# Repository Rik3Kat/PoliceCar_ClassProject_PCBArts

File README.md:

# PoliceCar_ClassProject_PCBArts

Here are the files for my PCB project.
The PCB consists of a simple curcuit: 

one 9V battery that powers everything

eight resistors
                                     
two capacitors
                                      
two transistors
                                      
two LED in the colour red and blue which alternately blink
                                       
four white LED which light up constantly

one slider switch which turns the lights of the curcuit on and off

The board of the PCB is designed in the shape of an old school police car. The curcuit and the footprint parts are fixed to the frontside of the board. 
The actual design of the PCB with the different layers is on the backside of the board.

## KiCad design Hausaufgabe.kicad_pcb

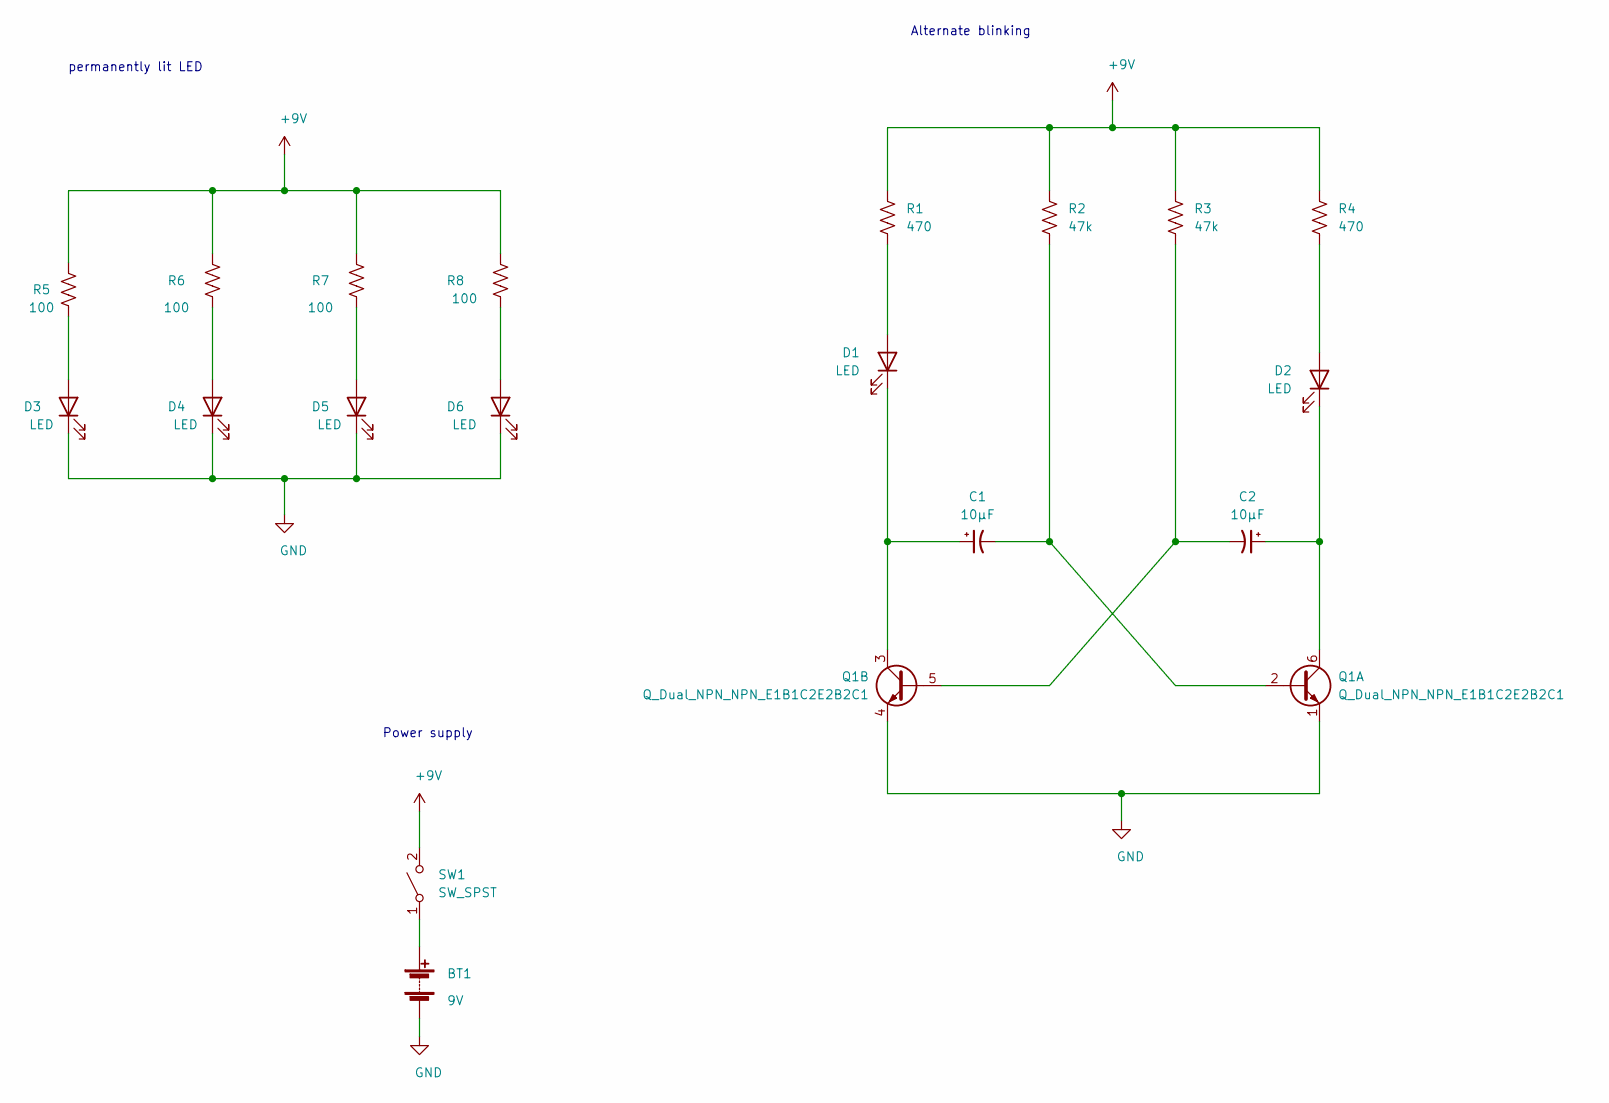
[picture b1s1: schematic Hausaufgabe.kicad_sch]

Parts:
BT1: 9V
C1, C2: 10μF; C_0805_2012Metric_Pad1.18x1.45mm_HandSolder
D1, D2, D3, D4, D5, D6: LED; custom_reverse_mount_LED
Q1: Q_Dual_NPN_NPN_E1B1C2E2B2C1; SOT-363_SC-70-6_Handsoldering
R1, R4: 470; R_0805_2012Metric_Pad1.20x1.40mm_HandSolder
R2, R3: 47k; R_0805_2012Metric_Pad1.20x1.40mm_HandSolder
R5, R6, R7, R8: 100; R_0805_2012Metric_Pad1.20x1.40mm_HandSolder
SW1: SW_SPST; CL-SB-22B

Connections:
+9V: R1.1, R2.1, R3.1, R4.1, R5.2, R6.2, R7.2, R8.2, SW1.2 (B)
GND: BT1.2 (-), D3.1 (K), D4.1 (K), D5.1 (K), D6.1 (K), Q1.1 (E1), Q1.4 (E2)
unnamed: BT1.1 (+), SW1.1 (A)
unnamed: C1.1, D1.1 (K), Q1.3 (C2)
unnamed: C1.2, Q1.2 (B1), R2.2
unnamed: C2.1, D2.1 (K), Q1.6 (C1)
unnamed: C2.2, Q1.5 (B2), R3.2
unnamed: D1.2 (A), R1.2
unnamed: D2.2 (A), R4.2
unnamed: D3.2 (A), R5.1
unnamed: D4.2 (A), R6.1
unnamed: D5.2 (A), R7.1
unnamed: D6.2 (A), R8.1

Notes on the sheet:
permanently lit LED
Power supply
Alternate blinking

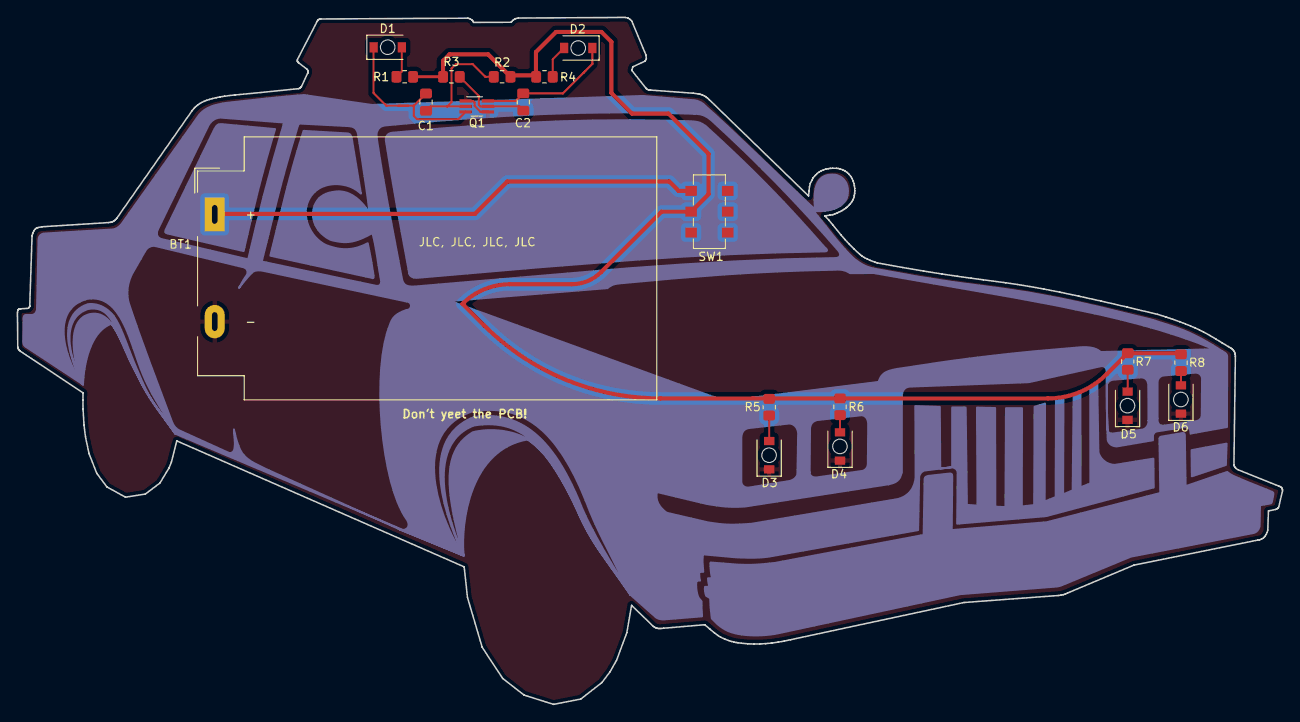
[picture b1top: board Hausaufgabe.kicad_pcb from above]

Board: 2 copper layers, 152.0 x 82.5 mm, 19 parts (0 on the bottom side), 13 nets.

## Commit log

2021-01-11 fixed typo
2021-01-13 comment about change
2021-01-14 fixed footprint and routing
2021-01-25 changed LED and switch footprint, cleaned up frontside of board
